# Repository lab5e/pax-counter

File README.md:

# PAX Counter

This device scans for visible bluetooth and wifi devices and then transmits the device count over NBIoT to a backend server.

IP67 version

Enclosure: [1555CF22GY](https://www.digikey.no/products/no?keywords=1555cf22) from Hammond Manufacturing

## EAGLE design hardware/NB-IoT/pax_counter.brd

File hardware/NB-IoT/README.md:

# IP67 PAX Counter

## BoM

* C1	10uF 0402
* C2	10uF 0402
* C3	0.1uF CAP_0402
* C4	10uF Tantalum 1206
* C5	100uF Tantalum 1206
* J1	FTDI_CONNECTOR
* R1	10k	0402
* R2	10k		0402
* S1	SWITCH PTS645
* U1	ESP-WROOM-32D
* U2	15 pin female header (2.54)
* U3	IRM-03-5
* U4    LM1117	SOT-223
* [1555CF22GY](https://www.digikey.no/products/no?keywords=1555cf22) enclosure

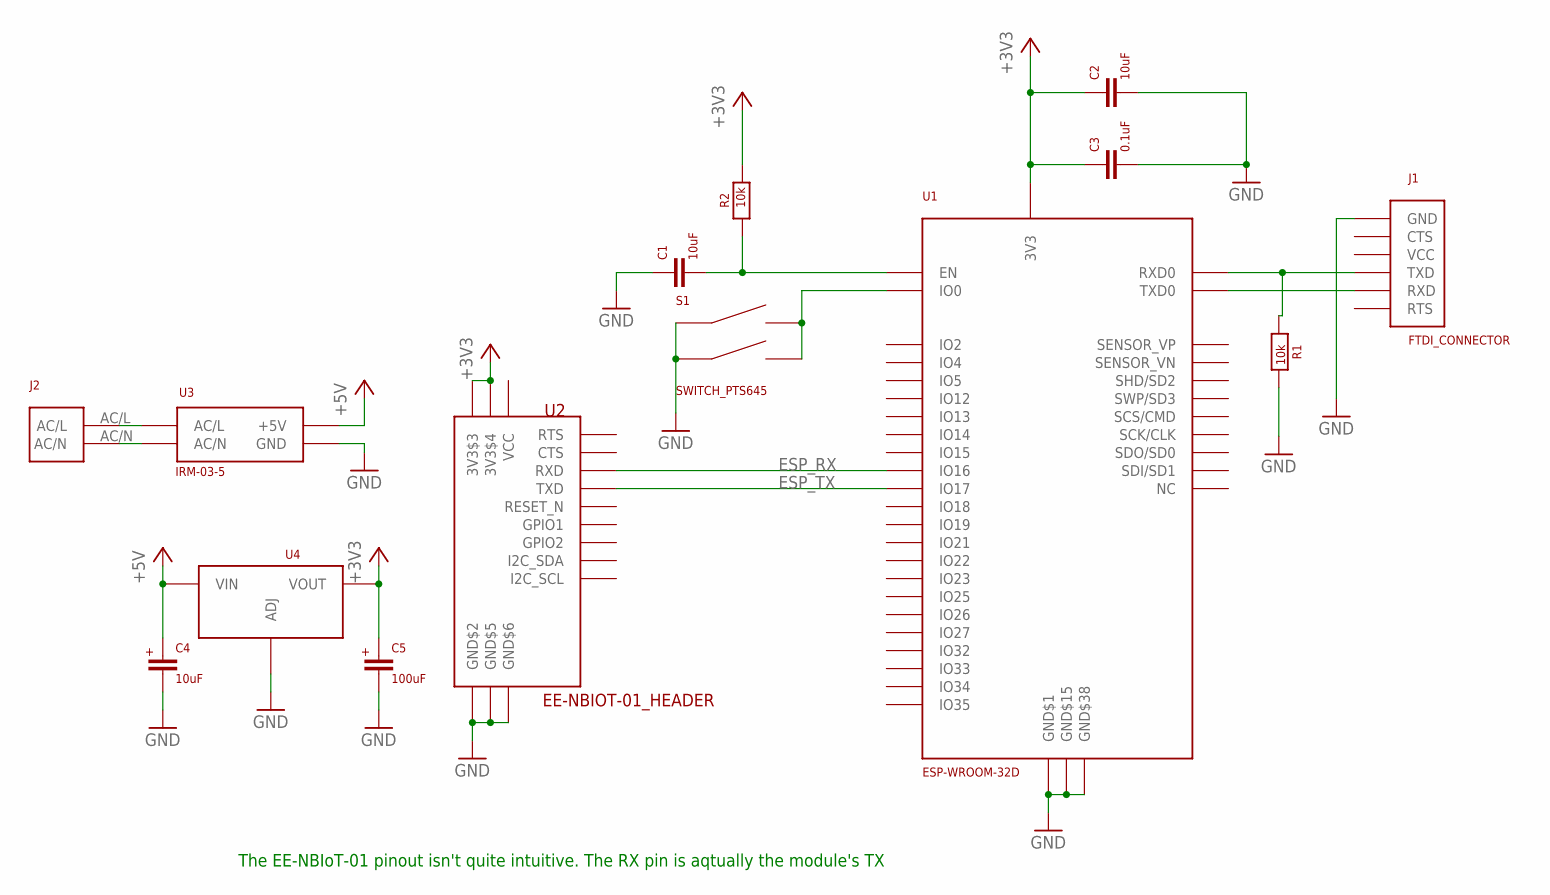
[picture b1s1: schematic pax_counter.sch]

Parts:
C1, C2: 10uF; CAP_0402
C3: 0.1uF; CAP_0402
C4: 10uF; TANTALUM_CAP_1206
C5: 100uF; TANTALUM_CAP_1206
J1: FTDI_CONNECTOR
J2: 240VAC_SOLDER_CONNECTOR
R1, R2: 10k; RES_0402
S1: SWITCH_PTS645; SWITCH_PTS645_EE_NBIOT_01
U1: ESP-WROOM-32D; ESP_WROOM_32D
U2: EE-NBIOT-01_HEADER
U3: IRM-03-5
U4: LM1117; SOT-223

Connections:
+3V3: C2.P$1 (1), C3.P$1 (1), C5.V+ (+), R2.P$2, U1.2 (3V3), U2.3V3$3, U2.3V3$4, U4.P$2 (VOUT), U4.VOUT$1 (VOUT)
+5V: C4.V+ (+), U3.+5V, U4.VIN
ESP_RX: U1.27 (IO16), U2.RXD
ESP_TX: U1.28 (IO17), U2.TXD
GND: C1.P$1 (1), C2.P$2 (2), C3.P$2 (2), C4.GND (-), C5.GND (-), J1.GND, R1.P$2, S1.A1, S1.A2, U1.1 (GND$1), U1.15 (GND$15), U1.38 (GND$38), U1.GND$39 (GND$38), U1.GND$40 (GND$38), U1.GND$41 (GND$38), U1.GND$42 (GND$38), U1.GND$43 (GND$38), U1.GND$44 (GND$38), U1.GND$45 (GND$38), U1.GND$46 (GND$38), U1.GND$47 (GND$38), U2.GND$2, U2.GND$5, U2.GND$6, U3.GND, U4.GND (ADJ)
unnamed: J2.AC/L, U3.AC/L
unnamed: J2.AC/N, U3.AC/N
unnamed: C1.P$2 (2), R2.P$1, U1.3 (EN)
unnamed: J1.TXD, R1.P$1, U1.34 (RXD0)
unnamed: J1.RXD, U1.35 (TXD0)
unnamed: S1.B1, S1.B2, U1.25 (IO0)

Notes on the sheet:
The EE-NBIoT-01 pinout isn't quite intuitive. The RX pin is aqtually the module's TX

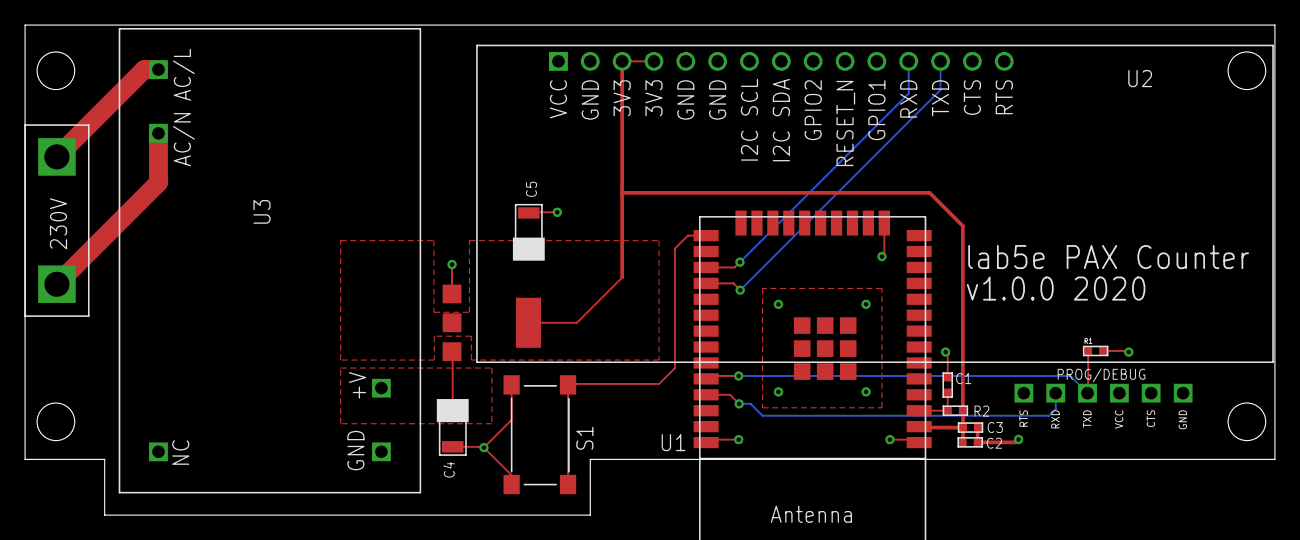
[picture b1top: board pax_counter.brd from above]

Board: 2 copper layers, 99.7 x 39.1 mm, 14 parts (0 on the bottom side), 11 nets.

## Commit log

2021-07-02 Updated with latest hardware design
    * Board definition
    * Schematics
    * Bill of materials
    * New images
2021-07-02 Moved eagle files for IP67 version
2021-07-02 Added readme for IP67 / NB-IoT version
    * Board image
    * Bill of materials
2021-07-02 Added protobuffer definition
2021-07-02 Added protobuffer encoding of payload
2021-07-05 Fixed APN
    * IP address debug output
    * Removed debug output
2021-07-06 Added time triggers for TX and reboot
2021-07-06 Added sensing of core temperature
    * extended message with core temperature reading
2021-07-06 Updated protobuffer
    * Added sequence number to messages
    * Added uptime to messages
2021-07-07 Updated partition table added BLE teardown func
    * Added mew README with links to newer versions of BLE framework
    classes
    * Added flag in platformio.ini for enabling HAL level logging
    * Added flag in platformio.ini for using custom partition table
    * Added teardown function for BLE
    * Added rudimentary logging in advertised callback (will use this in
2021-07-08 Work in progress (coap + partition magic)
    * added coap functions
    * extended partition table with app1 region
    * changed app partition size in order to fit everything within 4Mb
2021-11-09 Updated partition table
    * removed excessive logging in BLE scanner
2021-11-12 Partition table ok
    * 3 test sensors prepared
